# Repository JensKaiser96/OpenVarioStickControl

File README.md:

# Source Material

### [Orginal Projekt](https://www.openvario.org/doku.php?id=projects:remote_00:top)

### Komponenten
- PCB: 
  [Vorlage](https://github.com/adafruit/Adafruit_Atmega32u4_Breakout_Board)
 
- Buttons: \
  [RAFI 001.503 Kurzhubtaster, RACON 12, 42VAC/DC, SMD](https://www.reichelt.de/kurzhubtaster-racon-8-42vac-dc-smd-rafi-100-503-p110835.html)
  [Datenblatt](https://cdn-reichelt.de/documents/datenblatt/C200/DS_GER_RACON.pdf) \
  [Sollfahrt-Switch](https://www.reichelt.de/smd-kurzhubtaster-vert-montage-hoehe-5-0mm-taster-9315-p44514.html)
  
- [Joystick:  E-Switch JS5208](https://www.digikey.de/products/de?keywords=JS5208%20)

- [MicroController: ATMEGA32U4](https://www.digikey.de/product-detail/de/microchip-technology/ATMEGA32U4-AU/ATMEGA32U4-AU-ND/1914602)
  [Pin-mapping](https://www.arduino.cc/en/Hacking/PinMapping32u4)

- [Quarz: 7A-16.000MAAJ-T](https://www.digikey.de/product-detail/de/txc-corporation/7A-16.000MAAJ-T/887-1086-2-ND/2118770)
  
- [Sicherung: 04000025WR (500mA)](https://www.digikey.de/product-detail/de/04000025WR/F12131CT-ND/10271166)

### Sonstiges:
Bootloader: https://murchlabs.com/monday-experiment-bootloading-an-atmega32u4-with-arduino/

| Arduino Pin   | Atmega 32u4 Pin |
|:-------------:|:---------------:|
| 10      | 13  |
| 11      | 10  |
| 12      | 11  |
| 13      | 9   |
| 5V      | 5V  |
| GND     | GND |

1. Connect Arduino Uno to Atmega 32u4 according to the above Table
2. Connect Arduino Uno via USB to Computer
3. Start Ardinio IDE
4. Arduino as ISP, Leonardo Bootloader

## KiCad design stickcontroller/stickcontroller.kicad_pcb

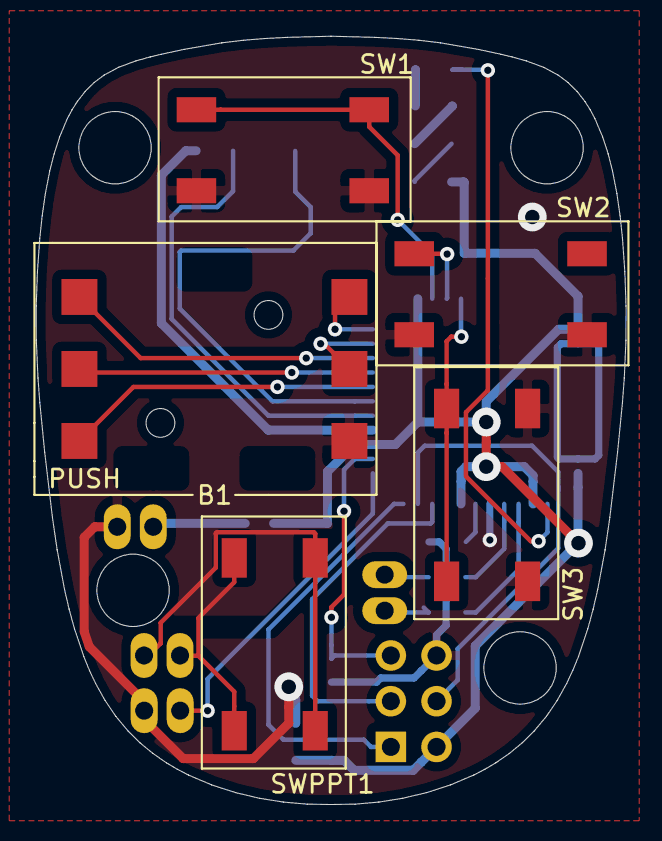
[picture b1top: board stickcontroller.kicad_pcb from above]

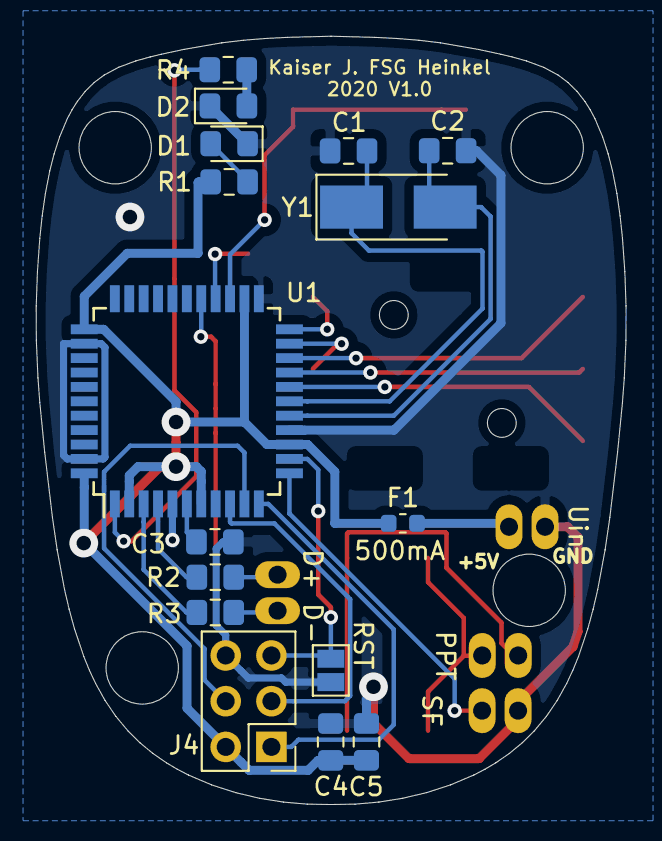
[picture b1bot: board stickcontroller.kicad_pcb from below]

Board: 2 copper layers, 32.7 x 42.7 mm, 25 parts (20 on the bottom side), 28 nets.

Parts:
B1: 4-direction-joystick; JS5208
C1, C2: 18pf; C_0805_2012Metric_Pad1.15x1.40mm_HandSolder
C3: 1uF; C_0805_2012Metric_Pad1.15x1.40mm_HandSolder
C4: 0.1uF; C_0805_2012Metric_Pad1.15x1.40mm_HandSolder
C5: 10uF; C_0805_2012Metric_Pad1.15x1.40mm_HandSolder
D1, D2: LED; LED_0805_2012Metric_Pad1.15x1.40mm_HandSolder
D+ D-: Conn_01x02; SolderWirePadOval_2
F1: 500mA; Fuse_0603_1608Metric
J4: Conn_02x03; PinHeader_2x03_P2.54mm_Vertical
PPT: Conn_01x02; SolderWirePadOval_2
R1, R4: 1K; R_0805_2012Metric_Pad1.15x1.40mm_HandSolder
R2, R3: 22; R_0805_2012Metric_Pad1.15x1.40mm_HandSolder
RST: Jumper_NO_Small; SolderJumper-2_P1.3mm_Open_Pad1.0x1.5mm
SF: Conn_01x02; SolderWirePadOval_2
SW1, SW2, SW3: SW_Push; Reichelt_RAFI_Kurzhubtaster
SWPPT1: SW_Push; Reichelt_RAFI_Kurzhubtaster
U1: ATmega32U4-AU; TQFP-44_10x10mm_P0.8mm
Uin: Conn_01x02; SolderWirePadOval_2
Y1: 16MHz; Crystal_SMD_5032-2Pin_5.0x3.2mm_HandSoldering

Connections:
+5V: C4.1, C5.1, F1.1, J4.2, R1.2, U1.2, U1.7, U1.14, U1.24, U1.34, U1.44
/D+: D+ D-.2, R2.2
/D-: D+ D-.1, R3.2
GND: B1.6, C1.2, C2.2, C3.2, C4.2, C5.2, D1.1, D2.1, J4.6, RST.1, SF.2, SW1.2, SW2.2, SW3.2, U1.5, U1.15, U1.23, U1.35, U1.43, Uin.1
unnamed: B1.1, U1.20
unnamed: B1.2, U1.19
unnamed: B1.3, U1.18
unnamed: B1.4, U1.22
unnamed: B1.5, U1.21
unnamed: C1.1, U1.17, Y1.1
unnamed: C2.1, U1.16, Y1.2
unnamed: C3.1, U1.6
unnamed: D1.2, R1.1
unnamed: D2.2, R4.1
unnamed: F1.2, Uin.2
unnamed: PPT.1, SWPPT1.2
unnamed: PPT.2, SWPPT1.1
unnamed: J4.1, U1.11
unnamed: J4.3, U1.9
unnamed: J4.4, U1.10
unnamed: J4.5, RST.2, U1.13
unnamed: SF.1, U1.12
unnamed: R2.1, U1.4
unnamed: R3.1, U1.3
unnamed: R4.2, U1.1
unnamed: SW1.1, U1.25
unnamed: SW2.1, U1.26
unnamed: SW3.1, U1.27

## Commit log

2020-01-20 kicad dateien
2021-01-14 Added Code File
